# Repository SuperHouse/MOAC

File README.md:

Mini Open Adaptive Controller
==============================

Universal input device that allows external switches, buttons, etc
to be connected using 3.5mm mono plugs, and then emulate a USB
keyboard, mouse, joystick, or game controller to send HID events
to a computer or game console.

This allows custom-made assistive-technology input devices to be
connected to a computer or game console. Functionally this is very
similar to the Microsoft Xbox Adaptive Controller, but with fewer
inputs, a fully open-source design, a display, and more device emulation
options.

Based on the ATmega32u4 microcontroller, compatible with the Arduino
Leonardo.

Features:

 * 8 switch inputs with 3.5mm mono sockets
 * USB-C socket for connection to computer, game controller, etc
 * Customise the software to suit your needs
 * 128x64 OLED module (SH1106)
 * ATmega 32u4 MCU (Arduino compatible)
 * Piezo beeper
 * Beep on/off switch
 * HWB (hardware boot) button and solder jumper to allow disabling bootloader

You can view more details at:

  http://www.superhouse.tv/moac

Hardware
--------
The "Hardware" directory contains the PCB design as an EAGLE project.
EAGLE PCB design software is available from Autodesk free for
non-commercial use.

Firmware
--------
The "Firmware" directory contains multiple versions. We have experimented
with different OLEDs and libraries during development, so this is a
collection of the different firmware versions.

The most recent hardware uses a 128x64 OLED with the SH1106 driver.

Unfortunately the various SH1106 drivers are a bit strange, and the best
I've found is the version of Adafruit's SSD1306 library that was forked
by wonho-maker and modified to add SSD1306 support. That version is not
available through the Arduino library manager, so it's been embedded
directly within the project.

Enclosure
---------
The "Enclosure" directory contains STLs for a case that can be
3D-printed.

The two halves of the case should be printed with the flat face down to
the printer bed.

The case can be held shut by countersunk self-tapping screws.

Credits
-------
 * Jonathan Oxer <jon@oxer.com.au>
 * Chris Fryer <chris.fryer78@gmail.com>

License
-------
Copyright 2018-2020 SuperHouse Automation Pty Ltd  www.superhouse.tv  

The hardware portion of this project is licensed under the TAPR Open
Hardware License (www.tapr.org/OHL). The "license" folder within this
repository contains a copy of this license in plain text format.

The software portion of this project is licensed under the Simplified
BSD License. The "licence" folder within this project contains a
copy of this license in plain text format.

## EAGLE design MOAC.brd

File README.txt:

Mini Open Adaptive Controller firmware
======================================

Firmware examples for the Mini Open Adaptive Controller. We have
experimented with different OLEDs and libraries during development,
so this is a collection of the different firmware versions.

The most recent hardware uses a 128x64 OLED with the SH1106 driver.

https://www.superhouse.tv/moac

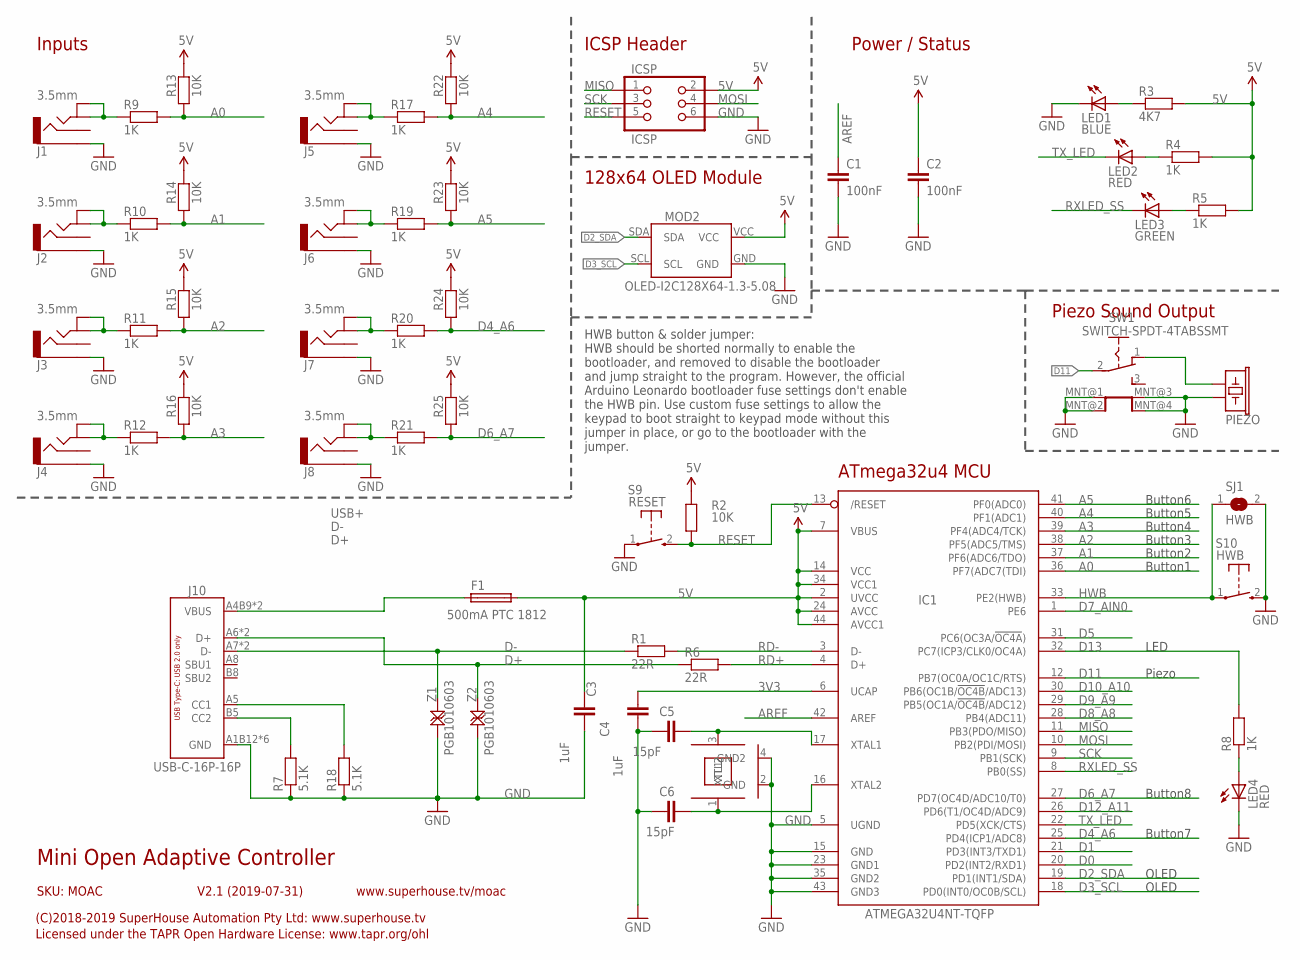
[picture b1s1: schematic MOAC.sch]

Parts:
C1, C2: 100nF; C0603
C3: 1uF; C0805
C4: 1uF; C0603
C5, C6: 15pF; C0603
F1: 500mA PTC 1812; 1812
IC1: ATMEGA32U4NT-TQFP; TQFP44
ICSP: ICSP; 2X03PTH
J1, J2, J3, J4, J5, J6, J7, J8: 3.5mm; AUDIO-JACK-PJ321
J10: USB-C-16P-16P; USB-C-16P
LED1: BLUE; LED-0603
LED2, LED4: RED; LED-0603
LED3: GREEN; LED-0603
MOD2: OLED-I2C128X64-1.3-5.08; OLED-128X64-1.3-5.08
PIEZO: BUZZERSMD12X12; BUZZER-12X12-SMT
R1, R6: 22R; R0603
R2, R13, R14, R15, R16, R22, R23, R24, R25: 10K; R0603
R3: 4K7; R0603
R4, R5, R8, R9, R10, R11, R12, R17, R19, R20, R21: 1K; R0603
R7, R18: 5.1K; R0603
S9: RESET; TACTILE_SMD_3X4X2
S10: HWB; TACTILE_SMD_3X4X2
SJ1: HWB; SJ
SW1: SWITCH-SPDT-4TABSSMT; MK-12C02
XTL1: 16MHz; CRYSTAL-SMD-3X2
Z1, Z2: PGB1010603; TVS0603

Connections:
3V3: C4.2, IC1.6 (UCAP)
5V: C2.1, C3.1, F1.2, IC1.2 (UVCC), IC1.7 (VBUS), IC1.14 (VCC), IC1.24 (AVCC), IC1.34 (VCC1), IC1.44 (AVCC1), ICSP.2, MOD2.VCC, R2.2, R3.2, R4.2, R5.2, R13.2, R14.2, R15.2, R16.2, R22.2, R23.2, R24.2, R25.2
A0: IC1.36 (PF7(ADC7(TDI)), R9.2, R13.1
A1: IC1.37 (PF6(ADC6/TDO)), R10.2, R14.1
A2: IC1.38 (PF5(ADC5/TMS)), R11.2, R15.1
A3: IC1.39 (PF4(ADC4/TCK)), R12.2, R16.1
A4: IC1.40 (PF1(ADC1)), R17.2, R22.1
A5: IC1.41 (PF0(ADC0)), R19.2, R23.1
AREF: C1.1, IC1.42 (AREF)
D0: IC1.20 (PD2(INT2/RXD1))
D1: IC1.21 (PD3(INT3/TXD1))
D2_SDA: IC1.19 (PD1(INT1/SDA)), MOD2.SDA
D3_SCL: IC1.18 (PD0(INT0/OC0B/SCL)), MOD2.SCL
D4_A6: IC1.25 (PD4(ICP1/ADC8)), R20.2, R24.1
D5: IC1.31 (PC6(OC3A/!OC4A!))
D6_A7: IC1.27 (PD7(OC4D/ADC10/T0)), R21.2, R25.1
D7_AIN0: IC1.1 (PE6)
D8_A8: IC1.28 (PB4(ADC11))
D9_A9: IC1.29 (PB5(OC1A/!OC4B!/ADC12))
D10_A10: IC1.30 (PB6(OC1B/!OC4B!/ADC13))
D11: IC1.12 (PB7(OC0A/OC1C/RTS)), SW1.2 (COM)
D12_A11: IC1.26 (PD6(T1/OC4D/ADC9))
D13: IC1.32 (PC7(ICP3/CLK0/OC4A)), R8.2
D+: J10.A6 (D+), J10.B6 (D+), R6.1, Z2.2
D-: J10.A7 (D-), J10.B7 (D-), R1.1, Z1.2
GND: C1.2, C2.2, C3.2, C4.1, C5.1, C6.1, IC1.5 (UGND), IC1.15 (GND), IC1.23 (GND1), IC1.35 (GND2), IC1.43 (GND3), ICSP.6, J1.3, J2.3, J3.3, J4.3, J5.3, J6.3, J7.3, J8.3, J10.A1B12 (GND), J10.A12B1 (GND), J10.FIX1 (GND), J10.FIX2 (GND), J10.FIX3 (GND), J10.FIX4 (GND), LED1.C, LED4.C, MOD2.GND, PIEZO.1, R7.1, R18.1, S9.1, S10.2 (S), SJ1.2, SW1.MNT@1 (MNT), SW1.MNT@2 (MNT), SW1.MNT@3 (MNT), SW1.MNT@4 (MNT), XTL1.2 (GND), XTL1.4 (GND2), Z1.1, Z2.1
HWB: IC1.33 (PE2(HWB)), S10.1, SJ1.1
MISO: IC1.11 (PB3(PDO/MISO)), ICSP.1
MOSI: IC1.10 (PB2(PDI/MOSI)), ICSP.4
unnamed: J10.B5 (CC2), R7.2
unnamed: LED4.A, R8.1
unnamed: J1.4A, J1.4B, R9.1
unnamed: J2.4A, J2.4B, R10.1
unnamed: J3.4A, J3.4B, R11.1
unnamed: LED1.A, R3.1
unnamed: LED2.A, R4.1
unnamed: LED3.A, R5.1
unnamed: J4.4A, J4.4B, R12.1
unnamed: J5.4A, J5.4B, R17.1
unnamed: C5.2, IC1.17 (XTAL1), XTL1.3 (XTL2)
unnamed: C6.2, IC1.16 (XTAL2), XTL1.1 (XTL1)
unnamed: J6.4A, J6.4B, R19.1
unnamed: J7.4A, J7.4B, R20.1
unnamed: J8.4A, J8.4B, R21.1
unnamed: PIEZO.2, SW1.1 (A)
unnamed: J10.A5 (CC1), R18.2
RD+: IC1.4 (D+), R6.2
RD-: IC1.3 (D-), R1.2
RESET: IC1.13 (/RESET), ICSP.5, R2.1, S9.2 (S)
RXLED_SS: IC1.8 (PB0(SS)), LED3.C
SCK: IC1.9 (PB1(SCK)), ICSP.3
TX_LED: IC1.22 (PD5(XCK/CTS)), LED2.C
USB+: F1.1, J10.A4B9 (VBUS), J10.A9B4 (VBUS)

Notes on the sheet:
ICSP Header
ATmega32u4 MCU
HWB button & solder jumper: HWB should be shorted normally to enable the bootloader, and removed to disable the bootloader and jump straight to the program. However, the official Arduino Leonardo bootloader fuse settings don't enable the HWB pin. Use custom fuse settings to allow the keypad to boot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
Mini Open Adaptive Controller
V2.1 (2019-07-31)
SKU: MOAC
(C)2018-2019 SuperHouse Automation Pty Ltd: www.superhouse.tv
Licensed under the TAPR Open Hardware License: www.tapr.org/ohl
www.superhouse.tv/moac
Power / Status
Button1
Button2
Button8
Button7
Button6
Button5
Button4
Inputs
Button3
128x64 OLED Module
Piezo Sound Output
Piezo
LED
OLED

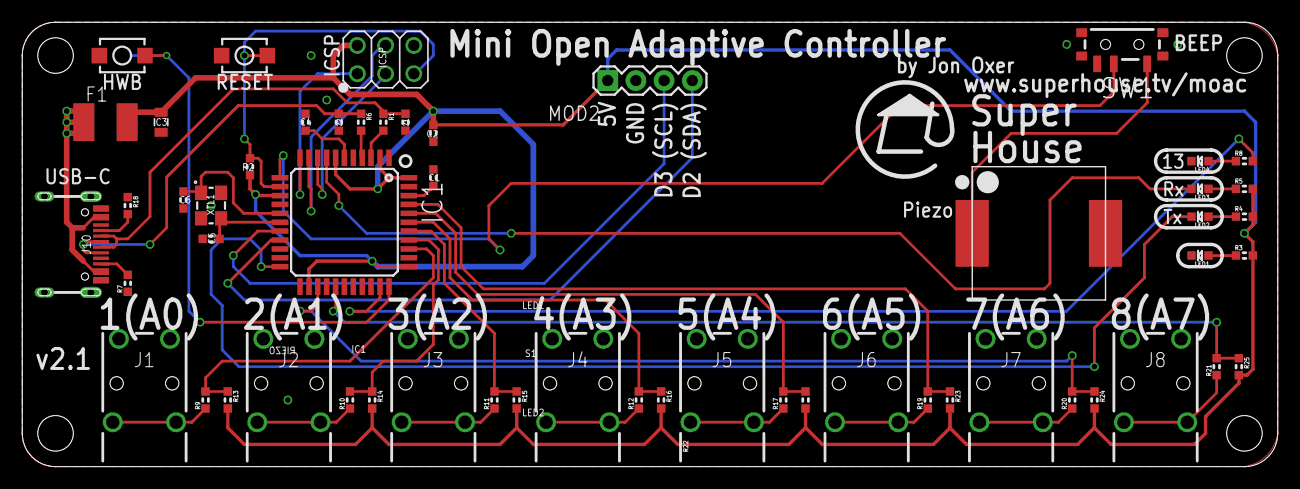
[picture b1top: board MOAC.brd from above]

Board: 2 copper layers, 113.0 x 40.0 mm, 56 parts (1 on the bottom side), 45 nets.

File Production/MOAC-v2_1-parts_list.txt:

Partlist

Exported from MOAC.sch at 16/7/20 12:54 PM

EAGLE Version 9.6.2 Copyright (c) 1988-2020 Autodesk, Inc.

Assembly variant: 

Part     Value                   Device                  Package              Library                 Sheet

C1       100nF                   CAP0603                 C0603                SuperHouse-DiscreteSemi 1
C2       100nF                   CAP0603                 C0603                SuperHouse-DiscreteSemi 1
C3       10uF                    CAP0805                 C0805                SuperHouse-DiscreteSemi 1
C4       1uF                     CAP0603                 C0603                SuperHouse-DiscreteSemi 1
C5       15pF                    CAP0603                 C0603                SuperHouse-DiscreteSemi 1
C6       15pF                    CAP0603                 C0603                SuperHouse-DiscreteSemi 1
F1       500mA PTC 1812          PTC050                  1812                 SuperHouse-Fuses        1
IC1      ATMEGA32U4NT-TQFP       ATMEGA32U4NT-TQFP       TQFP44               SuperHouse-MCUs         1
ICSP     ICSP                    ICSPPTH                 2X03PTH              SuperHouse-Connectors   1
J1       3.5mm                   AUDIO-JACK-PJ321        AUDIO-JACK-PJ321     SuperHouse-Connectors   1
J2       3.5mm                   AUDIO-JACK-PJ321        AUDIO-JACK-PJ321     SuperHouse-Connectors   1
J3       3.5mm                   AUDIO-JACK-PJ321        AUDIO-JACK-PJ321     SuperHouse-Connectors   1
J4       3.5mm                   AUDIO-JACK-PJ321        AUDIO-JACK-PJ321     SuperHouse-Connectors   1
J5       3.5mm                   AUDIO-JACK-PJ321        AUDIO-JACK-PJ321     SuperHouse-Connectors   1
J6       3.5mm                   AUDIO-JACK-PJ321        AUDIO-JACK-PJ321     SuperHouse-Connectors   1
J7       3.5mm                   AUDIO-JACK-PJ321        AUDIO-JACK-PJ321     SuperHouse-Connectors   1
J8       3.5mm                   AUDIO-JACK-PJ321        AUDIO-JACK-PJ321     SuperHouse-Connectors   1
J10      USB-C-16P-16P           USB-C-16P-16P           USB-C-16P            SuperHouse-Connectors   1
LED1     BLUE                    LED0603                 LED-0603             SuperHouse-LEDs         1
LED2     RED                     LED0603                 LED-0603             SuperHouse-LEDs         1
LED3     GREEN                   LED0603                 LED-0603             SuperHouse-LEDs         1
LED4     RED                     LED0603                 LED-0603             SuperHouse-LEDs         1
MOD2     OLED-I2C128X64-1.3-5.08 OLED-I2C128X64-1.3-5.08 OLED-128X64-1.3-5.08 SuperHouse-Displays     1
PIEZO    BUZZERSMD12X12          BUZZERSMD12X12          BUZZER-12X12-SMT     SuperHouse-Audio        1
R1       22R                     RESISTOR0603            R0603                SuperHouse-DiscreteSemi 1
R2       10K                     RESISTOR0603            R0603                SuperHouse-DiscreteSemi 1
R3       4K7                     RESISTOR0603            R0603                SuperHouse-DiscreteSemi 1
R4       1K                      RESISTOR0603            R0603                SuperHouse-DiscreteSemi 1
R5       1K                      RESISTOR0603            R0603                SuperHouse-DiscreteSemi 1
R6       22R                     RESISTOR0603            R0603                SuperHouse-DiscreteSemi 1
R7       5.1K                    RESISTOR0603            R0603                SuperHouse-DiscreteSemi 1
R8       1K                      RESISTOR0603            R0603                SuperHouse-DiscreteSemi 1
R9       1K                      RESISTOR0603            R0603                SuperHouse-DiscreteSemi 1
R10      1K                      RESISTOR0603            R0603                SuperHouse-DiscreteSemi 1
R11      1K                      RESISTOR0603            R0603                SuperHouse-DiscreteSemi 1
R12      1K                      RESISTOR0603            R0603                SuperHouse-DiscreteSemi 1
R13      10K                     RESISTOR0603            R0603                SuperHouse-DiscreteSemi 1
R14      10K                     RESISTOR0603            R0603                SuperHouse-DiscreteSemi 1
R15      10K                     RESISTOR0603            R0603                SuperHouse-DiscreteSemi 1
R16      10K                     RESISTOR0603            R0603                SuperHouse-DiscreteSemi 1
R17      1K                      RESISTOR0603            R0603                SuperHouse-DiscreteSemi 1
R18      5.1K                    RESISTOR0603            R0603                SuperHouse-DiscreteSemi 1
R19      1K                      RESISTOR0603            R0603                SuperHouse-DiscreteSemi 1
R20      1K                      RESISTOR0603            R0603                SuperHouse-DiscreteSemi 1
R21      1K                      RESISTOR0603            R0603                SuperHouse-DiscreteSemi 1
R22      10K                     RESISTOR0603            R0603                SuperHouse-DiscreteSemi 1
R23      10K                     RESISTOR0603            R0603                SuperHouse-DiscreteSemi 1
R24      10K                     RESISTOR0603            R0603                SuperHouse-DiscreteSemi 1
R25      10K                     RESISTOR0603            R0603                SuperHouse-DiscreteSemi 1
S9       RESET                   TAC_SWITCH_2PINSMT      TACTILE_SMD_3X4X2    SuperHouse-Switches     1
S10      HWB                     TAC_SWITCH_2PINSMT      TACTILE_SMD_3X4X2    SuperHouse-Switches     1
SJ1      HWB                     SJ-NORMAL               SJ                   SuperHouse-Jumpers      1
SW1      SWITCH-SPDT-4TABSSMT    SWITCH-SPDT-4TABSSMT    MK-12C02             SuperHouse-Switches     1
XTL1     16MHz                   CRYSTAL-GND3X2          CRYSTAL-SMD-3X2      SuperHouse-Oscillators  1
Z1       PGB1010603              TVS0603                 TVS0603              SuperHouse-DiscreteSemi 1
Z2       PGB1010603              TVS0603                 TVS0603              SuperHouse-DiscreteSemi 1

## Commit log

2018-11-14 Initial project import for v1.0 release
2018-11-24 Improved designators
2019-07-07 Replaced parts using SuperHouse libraries to add 3D models
2019-07-11 Replaced 128x32 OLED with 128x64, 1.3in for v2.0 release
2019-07-18 Changed ATmega32U4 from QFN to TQFP to save Jon's sanity for v2.0 release
2019-07-31 Changed button 8 from A11 to A7, to fix Jon's silly mistake from way back in v1.0
2019-11-04 Initial import of test sketches
2020-03-18 Changed display from 128x32 to 128x64
2020-05-05 Embedded forked SH1106 library
2020-05-05 Note about embedded library
2020-05-05 Moved config into separate file
2020-05-05 Moved config to external file; added piezo beep; coding standards fixes
2020-05-05 File format
2020-05-05 Added piezo switch; replaced USB-C socket for v2.1 release
2020-05-12 Final tweaks and DRC for v2.1 release
2020-05-12 Added stencil DXF for v2.1
2020-07-14 Added config options for audible feedback
2020-07-14 Begin restructuring project to merge hardware and software into one repository
2020-07-14 Moved files into subdirectory prior to merging with overall project
2020-07-14 Added enclosure STLs
2020-07-14 Merged docs into single README
2020-07-14 Added image
2020-07-14 Added resources
2020-07-14 Added Simplified BSD License for software portion
2020-07-16 Changed decoupling cap to 10uF
2020-07-16 Improved description
2020-07-16 Added image of MOAC and XAC together
2020-07-16 Added beep switch slot to case
2020-07-16 Added input labels and URL to enclosure
2020-07-16 Removed backup EAGLE files
2020-07-16 Spelling
2020-07-22 Added packaging hang tag label
2020-07-22 Added project URL to example output
2020-07-22 Added input numbers and URL to case
2020-07-22 Added ignore file
2020-07-22 Added v2.1 photos
2020-08-10 Deleted image
2021-01-05 Replaced built-in mouse library with Nico Hood's USB HID library. Added mouse warp feature.
2021-01-05 Added timesheet to gitignore

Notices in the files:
MOAC.brd:
Copyright 2018-2019 SuperHouse Automation Pty Ltd
Released under the TAPR Open Hardware License
